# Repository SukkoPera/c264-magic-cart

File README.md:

# c264-magic-cart 44-pin

c264-magic-cart is a cartridge for the Commodore 264 series of computers - Commodore 16, 116 and Plus/4.

## Summary
This is a 44-pin variant of [the original project by Marko Šolajić](https://github.com/msolajic/c264-magic-cart).

This version is still aimed at the C16/C116/Plus4 and it **requires** the usage of a [Plus4MultiExpander](https://github.com/SukkoPera/Plus4MultiExpander) or something similar. It is NOT compatible with the C64/C128.

Isn't Open Hardware great?

## Usage
The project was migrated to KiCad, during which the nice graphics were lost. Apart from that and changing the connector, I only made minor modifications, mostly to switch to standard KiCad footprints.

The only significant difference is the introduction of JP4 and JP5 in order to run the cartridge from the C2 slot. This is experimental and untested, so just set them both to center-left in order to run from the C1 slot as the original project does.

If you plan to use this at the same time as the EPROM slot on [TCBM2SD](https://github.com/SukkoPera/tcbm2sd-44pin), you will probably need an updated JED file for the latter, which is yet unreleased at the time of writing, so please check again later.

Please refer to [the original project](https://github.com/msolajic/c264-magic-cart) for GAL files, documentation, instructions, etc.

## Releases
If you want to get this board produced, you are recommended to get [the latest release](https://github.com/SukkoPera/c264-magic-cart-44pin/releases) rather than the current git version, as the latter might be under development and is not guaranteed to be working.

Every release is accompanied by its Bill Of Materials (BOM) file and any relevant notes about it, which you are recommended to read carefully.

## License
The original c264-magic-cart is Open Hardware licensed under the [CERN OHL v. 1.2](https://spdx.org/licenses/CERN-OHL-1.2.html), released by Marko Šolajić in 2021.

This 44-pin version is copyright &copy; SukkoPera 2026 and is licensed under the same license.

## Thanks
- Marko for his amazing work.
- Tadeusz Klimaszewski for coming up with the idea of porting this project to the 44-pin connector and testing it.

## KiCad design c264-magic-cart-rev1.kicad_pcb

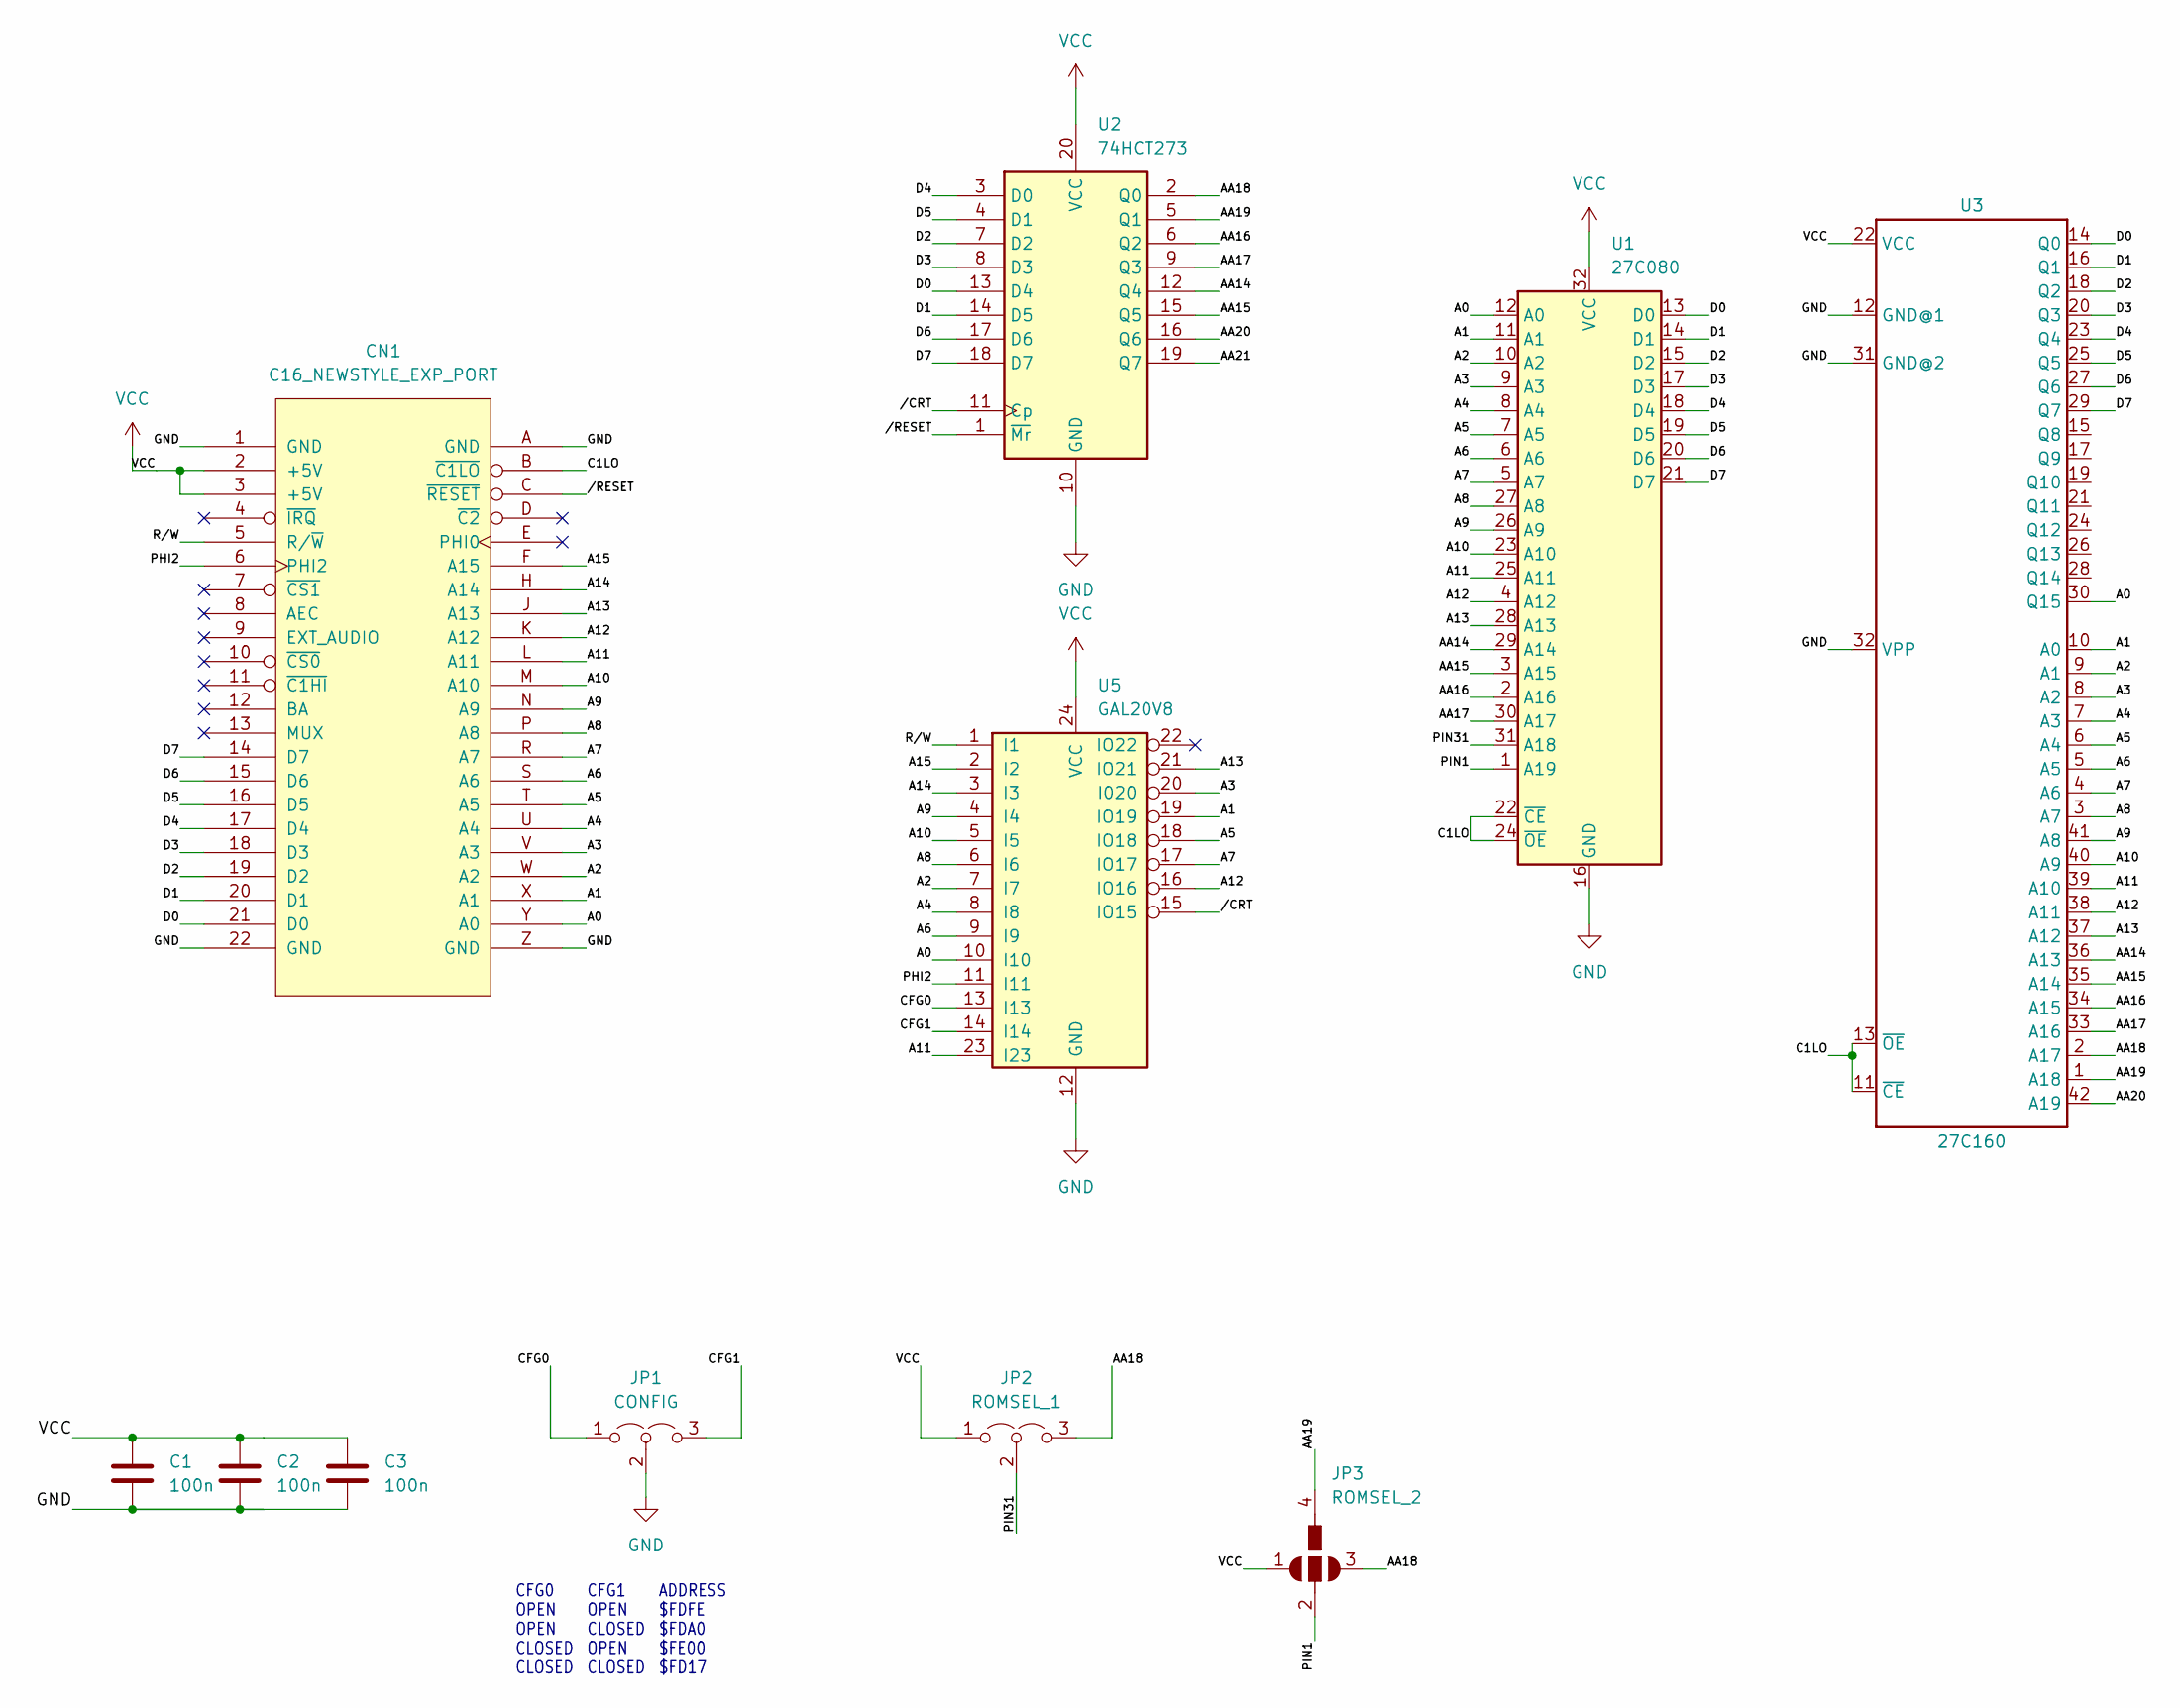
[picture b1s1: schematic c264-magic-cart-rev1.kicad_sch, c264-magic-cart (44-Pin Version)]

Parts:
C1, C2, C3: 100n; C_Disc_D7.5mm_W2.5mm_P5.00mm
CN1: C16_NEWSTYLE_EXP_PORT; EdgeConn-44pin
JP1: CONFIG; SolderJumper-3_P1.3mm_Open_Pad1.0x1.5mm
JP2: ROMSEL_1; SolderJumper-3_P1.3mm_Open_Pad1.0x1.5mm
JP3: ROMSEL_2; SJ_3
U1: 27C080; DIP-32_W15.24mm_Socket
U2: 74HCT273; DIP-20_W7.62mm_Socket_LongPads
U3: 27C160; DIP-42_W15.24mm_Socket
U5: GAL20V8; DIP-24_W7.62mm_Socket_LongPads

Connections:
/A0: CN1.Y (A0), U1.12 (A0), U3.30 (Q15), U5.10 (I10)
/A1: CN1.X (A1), U1.11 (A1), U3.10 (A0), U5.19 (IO19)
/A2: CN1.W (A2), U1.10 (A2), U3.9 (A1), U5.7 (I7)
/A3: CN1.V (A3), U1.9 (A3), U3.8 (A2), U5.20 (I020)
/A4: CN1.U (A4), U1.8 (A4), U3.7 (A3), U5.8 (I8)
/A5: CN1.T (A5), U1.7 (A5), U3.6 (A4), U5.18 (IO18)
/A6: CN1.S (A6), U1.6 (A6), U3.5 (A5), U5.9 (I9)
/A7: CN1.R (A7), U1.5 (A7), U3.4 (A6), U5.17 (IO17)
/A8: CN1.P (A8), U1.27 (A8), U3.3 (A7), U5.6 (I6)
/A9: CN1.N (A9), U1.26 (A9), U3.41 (A8), U5.4 (I4)
/A10: CN1.M (A10), U1.23 (A10), U3.40 (A9), U5.5 (I5)
/A11: CN1.L (A11), U1.25 (A11), U3.39 (A10), U5.23 (I23)
/A12: CN1.K (A12), U1.4 (A12), U3.38 (A11), U5.16 (IO16)
/A13: CN1.J (A13), U1.28 (A13), U3.37 (A12), U5.21 (IO21)
/A14: CN1.H (A14), U5.3 (I3)
/A15: CN1.F (A15), U5.2 (I2)
/AA14: U1.29 (A14), U2.12 (Q4), U3.36 (A13)
/AA15: U1.3 (A15), U2.15 (Q5), U3.35 (A14)
/AA16: U1.2 (A16), U2.6 (Q2), U3.34 (A15)
/AA17: U1.30 (A17), U2.9 (Q3), U3.33 (A16)
/AA18: JP2.3 (B), JP3.3, U2.2 (Q0), U3.2 (A17)
/AA19: JP3.4, U2.5 (Q1), U3.1 (A18)
/AA20: U2.16 (Q6), U3.42 (A19)
/AA21: U2.19 (Q7)
/C1LO: CN1.B (~C1LO), U1.22 (~CE), U1.24 (~OE), U3.11 (~CE), U3.13 (~OE)
/CFG0: JP1.1 (A), U5.13 (I13)
/CFG1: JP1.3 (B), U5.14 (I14)
/D0: CN1.21 (D0), U1.13 (D0), U2.13 (D4), U3.14 (Q0)
/D1: CN1.20 (D1), U1.14 (D1), U2.14 (D5), U3.16 (Q1)
/D2: CN1.19 (D2), U1.15 (D2), U2.7 (D2), U3.18 (Q2)
/D3: CN1.18 (D3), U1.17 (D3), U2.8 (D3), U3.20 (Q3)
/D4: CN1.17 (D4), U1.18 (D4), U2.3 (D0), U3.23 (Q4)
/D5: CN1.16 (D5), U1.19 (D5), U2.4 (D1), U3.25 (Q5)
/D6: CN1.15 (D6), U1.20 (D6), U2.17 (D6), U3.27 (Q6)
/D7: CN1.14 (D7), U1.21 (D7), U2.18 (D7), U3.29 (Q7)
/PHI2: CN1.6 (PHI2), U5.11 (I11)
/PIN1: JP3.2, U1.1 (A19)
/PIN31: JP2.2 (C), U1.31 (A18)
/R/W: CN1.5 (R/~W), U5.1 (I1)
//CRT: U2.11 (Cp), U5.15 (IO15)
//RESET: CN1.C (~RESET), U2.1 (~Mr)
GND: C1.2, C2.2, C3.2, CN1.1 (GND), CN1.22 (GND), CN1.A (GND), CN1.Z (GND), JP1.2 (C), U1.16 (GND), U2.10 (GND), U3.12 (GND@1), U3.31 (GND@2), U3.32 (VPP), U5.12 (GND)
VCC: C1.1, C2.1, C3.1, CN1.2 (+5V), CN1.3 (+5V), JP2.1 (A), JP3.1, U1.32 (VCC), U2.20 (VCC), U3.22 (VCC), U5.24 (VCC)

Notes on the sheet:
ADDRESS $FDFE $FDA0 $FE00 $FD17
CFG1 OPEN CLOSED OPEN CLOSED
CFG0 OPEN OPEN CLOSED CLOSED

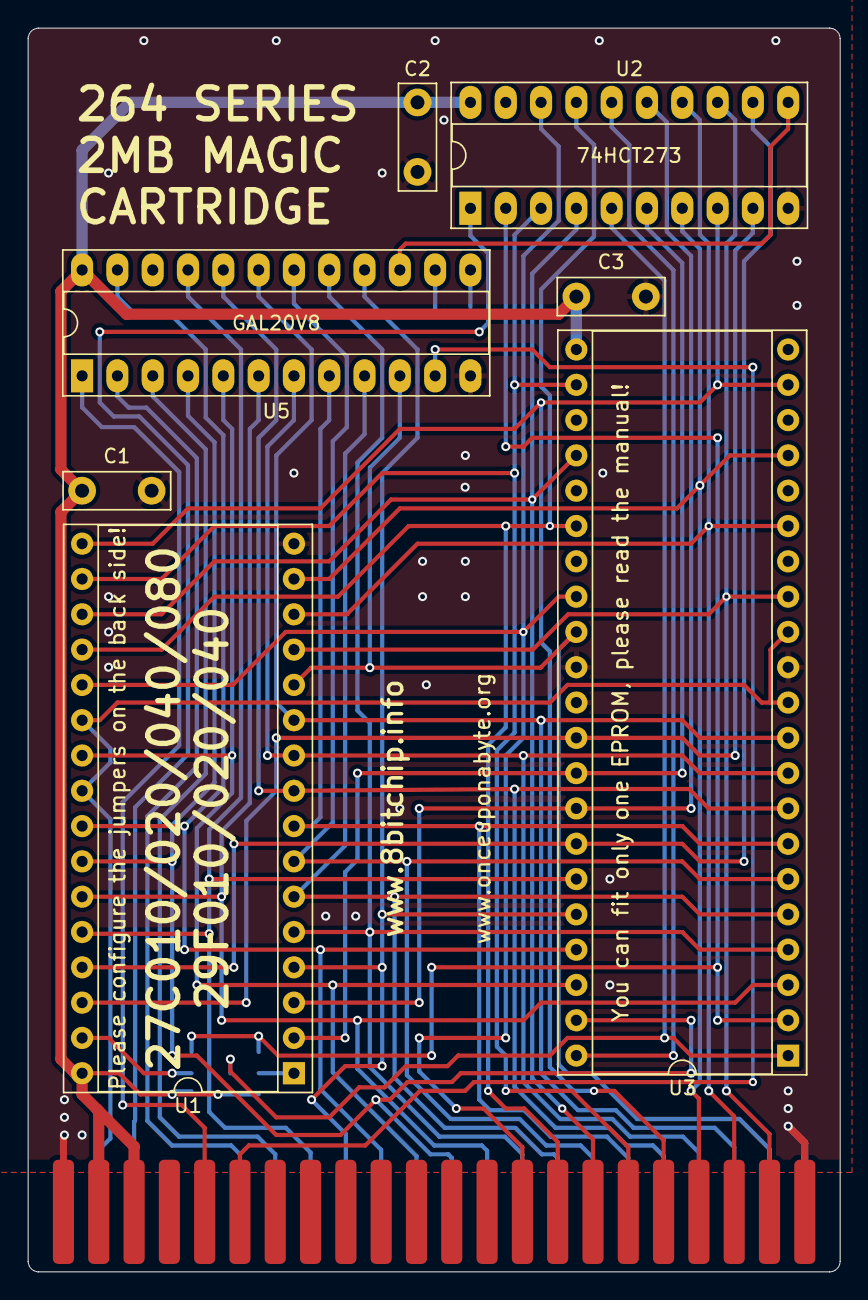
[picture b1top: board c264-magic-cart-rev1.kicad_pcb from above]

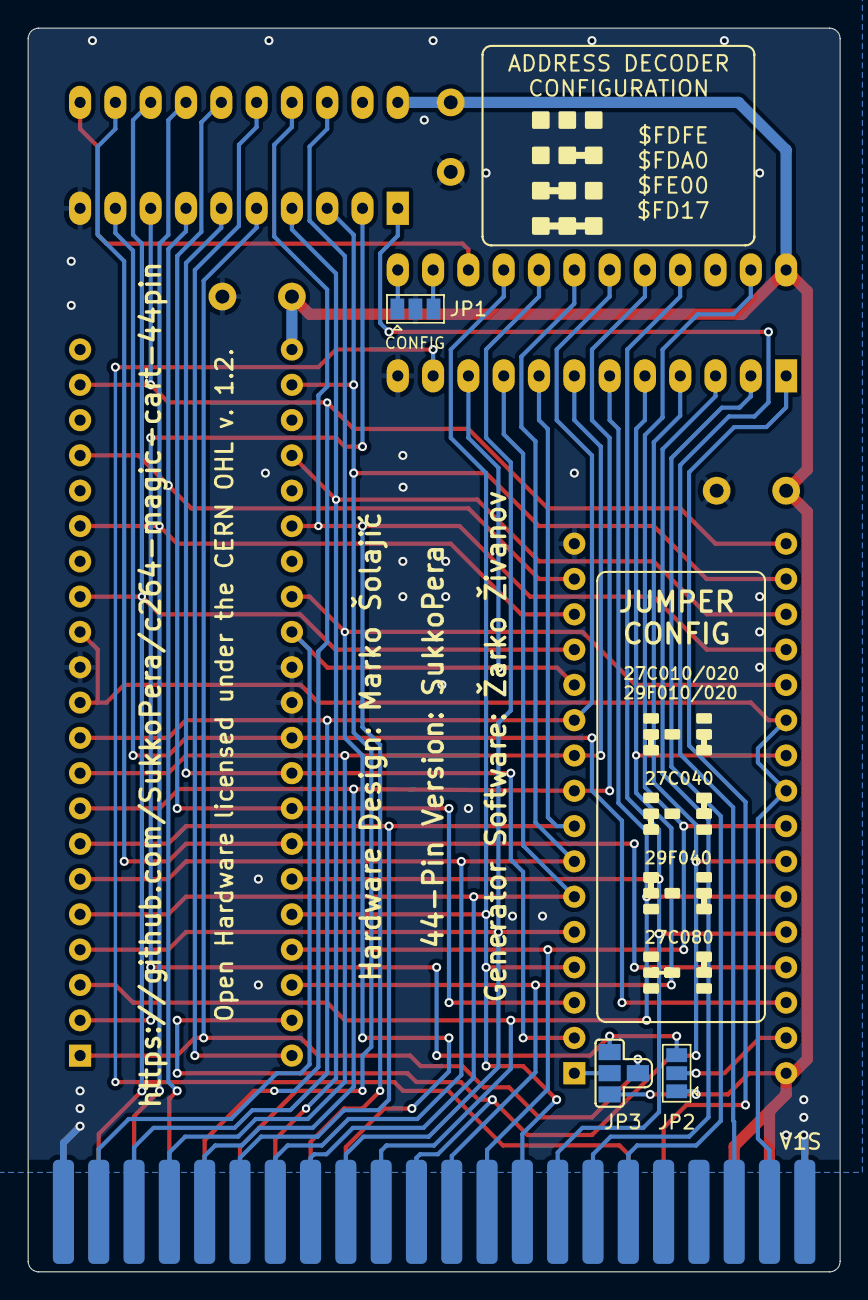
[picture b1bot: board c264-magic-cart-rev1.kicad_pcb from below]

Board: 2 copper layers, 58.4 x 89.5 mm, 11 parts (3 on the bottom side), 42 nets.

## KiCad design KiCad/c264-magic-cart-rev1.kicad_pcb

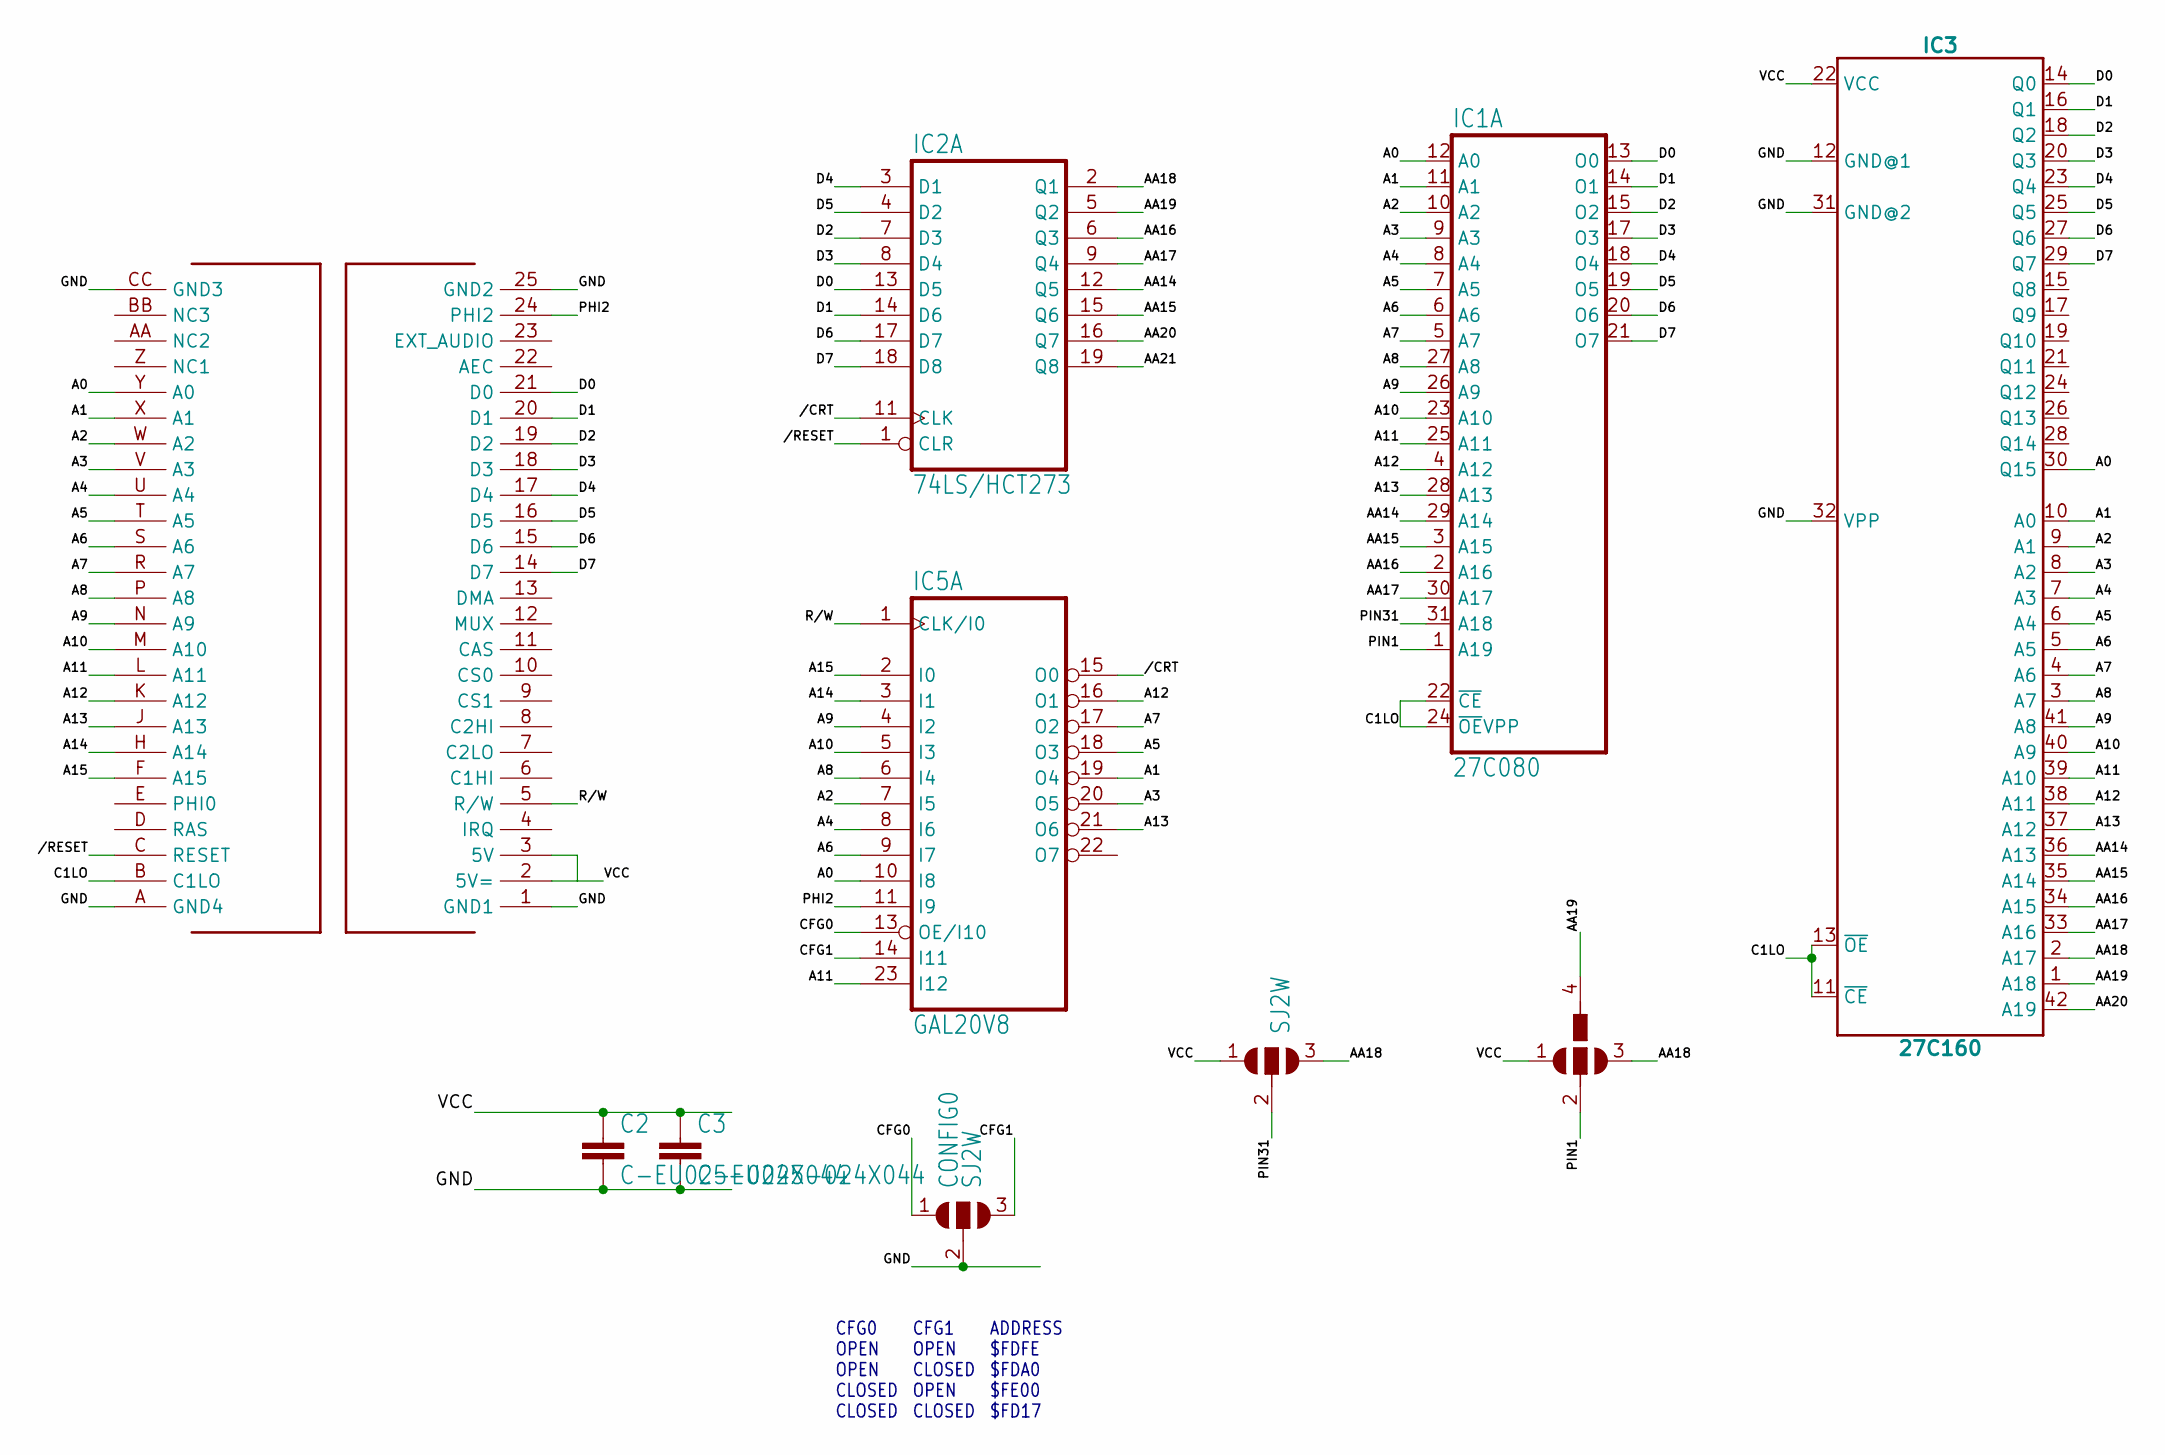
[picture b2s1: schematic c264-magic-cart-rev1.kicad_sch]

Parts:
C2, C3: C-EU025-024X044; C025-024X044
CONFIG0: SJ2W; SJ_2
IC1: 27C080; DIL32
IC2: 74LS/HCT273; DIL20
IC3: 27C160; DIP42
IC5: GAL20V8; DIL24-3
SJ1: SJ2W; SJ_2
U$1: C16_CARTRIDGE; C16_CART
U$2: SJ3; SJ_3

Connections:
/CRT: IC2.11 (CLK), IC5.15 (O0)
/RESET: IC2.1 (CLR), U$1.C (RESET)
A0: IC1.12 (A0), IC3.30 (Q15), IC5.10 (I8), U$1.Y (A0)
A1: IC1.11 (A1), IC3.10 (A0), IC5.19 (O4), U$1.X (A1)
A2: IC1.10 (A2), IC3.9 (A1), IC5.7 (I5), U$1.W (A2)
A3: IC1.9 (A3), IC3.8 (A2), IC5.20 (O5), U$1.V (A3)
A4: IC1.8 (A4), IC3.7 (A3), IC5.8 (I6), U$1.U (A4)
A5: IC1.7 (A5), IC3.6 (A4), IC5.18 (O3), U$1.T (A5)
A6: IC1.6 (A6), IC3.5 (A5), IC5.9 (I7), U$1.S (A6)
A7: IC1.5 (A7), IC3.4 (A6), IC5.17 (O2), U$1.R (A7)
A8: IC1.27 (A8), IC3.3 (A7), IC5.6 (I4), U$1.P (A8)
A9: IC1.26 (A9), IC3.41 (A8), IC5.4 (I2), U$1.N (A9)
A10: IC1.23 (A10), IC3.40 (A9), IC5.5 (I3), U$1.M (A10)
A11: IC1.25 (A11), IC3.39 (A10), IC5.23 (I12), U$1.L (A11)
A12: IC1.4 (A12), IC3.38 (A11), IC5.16 (O1), U$1.K (A12)
A13: IC1.28 (A13), IC3.37 (A12), IC5.21 (O6), U$1.J (A13)
A14: IC5.3 (I1), U$1.H (A14)
A15: IC5.2 (I0), U$1.F (A15)
AA14: IC1.29 (A14), IC2.12 (Q5), IC3.36 (A13)
AA15: IC1.3 (A15), IC2.15 (Q6), IC3.35 (A14)
AA16: IC1.2 (A16), IC2.6 (Q3), IC3.34 (A15)
AA17: IC1.30 (A17), IC2.9 (Q4), IC3.33 (A16)
AA18: IC2.2 (Q1), IC3.2 (A17), SJ1.3, U$2.3
AA19: IC2.5 (Q2), IC3.1 (A18), U$2.4
AA20: IC2.16 (Q7), IC3.42 (A19)
AA21: IC2.19 (Q8)
C1LO: IC1.22 (~CE), IC1.24 (~OEVPP), IC3.11 (~CE), IC3.13 (~OE), U$1.B (C1LO)
CFG0: CONFIG0.1, IC5.13 (OE/I10)
CFG1: CONFIG0.3, IC5.14 (I11)
D0: IC1.13 (O0), IC2.13 (D5), IC3.14 (Q0), U$1.21 (D0)
D1: IC1.14 (O1), IC2.14 (D6), IC3.16 (Q1), U$1.20 (D1)
D2: IC1.15 (O2), IC2.7 (D3), IC3.18 (Q2), U$1.19 (D2)
D3: IC1.17 (O3), IC2.8 (D4), IC3.20 (Q3), U$1.18 (D3)
D4: IC1.18 (O4), IC2.3 (D1), IC3.23 (Q4), U$1.17 (D4)
D5: IC1.19 (O5), IC2.4 (D2), IC3.25 (Q5), U$1.16 (D5)
D6: IC1.20 (O6), IC2.17 (D7), IC3.27 (Q6), U$1.15 (D6)
D7: IC1.21 (O7), IC2.18 (D8), IC3.29 (Q7), U$1.14 (D7)
GND: C2.2, C3.2, CONFIG0.2, IC1.16 (GND), IC2.10 (GND), IC3.12 (GND@1), IC3.31 (GND@2), IC3.32 (VPP), IC5.12 (GND), U$1.1 (GND1), U$1.25 (GND2), U$1.A (GND4), U$1.CC (GND3)
PHI2: IC5.11 (I9), U$1.24 (PHI2)
PIN1: IC1.1 (A19), U$2.2
PIN31: IC1.31 (A18), SJ1.2
R/W: IC5.1 (CLK/I0), U$1.5 (R/W)
VCC: C2.1, C3.1, IC1.32 (VCC), IC2.20 (VCC), IC3.22 (VCC), IC5.24 (VCC), SJ1.1, U$1.2 (5V=), U$1.3 (5V), U$2.1

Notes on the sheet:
ADDRESS $FDFE $FDA0 $FE00 $FD17
CFG1 OPEN CLOSED OPEN CLOSED
CFG0 OPEN OPEN CLOSED CLOSED

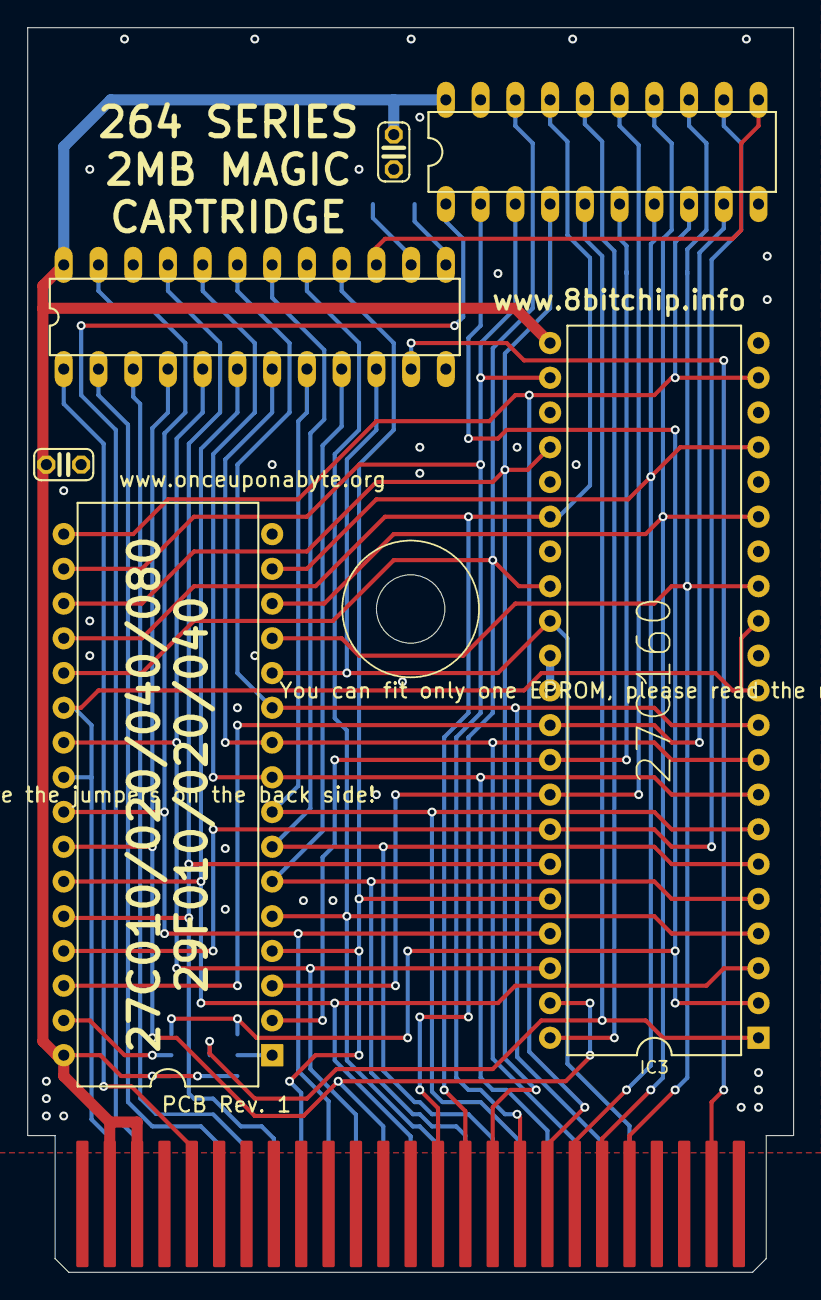
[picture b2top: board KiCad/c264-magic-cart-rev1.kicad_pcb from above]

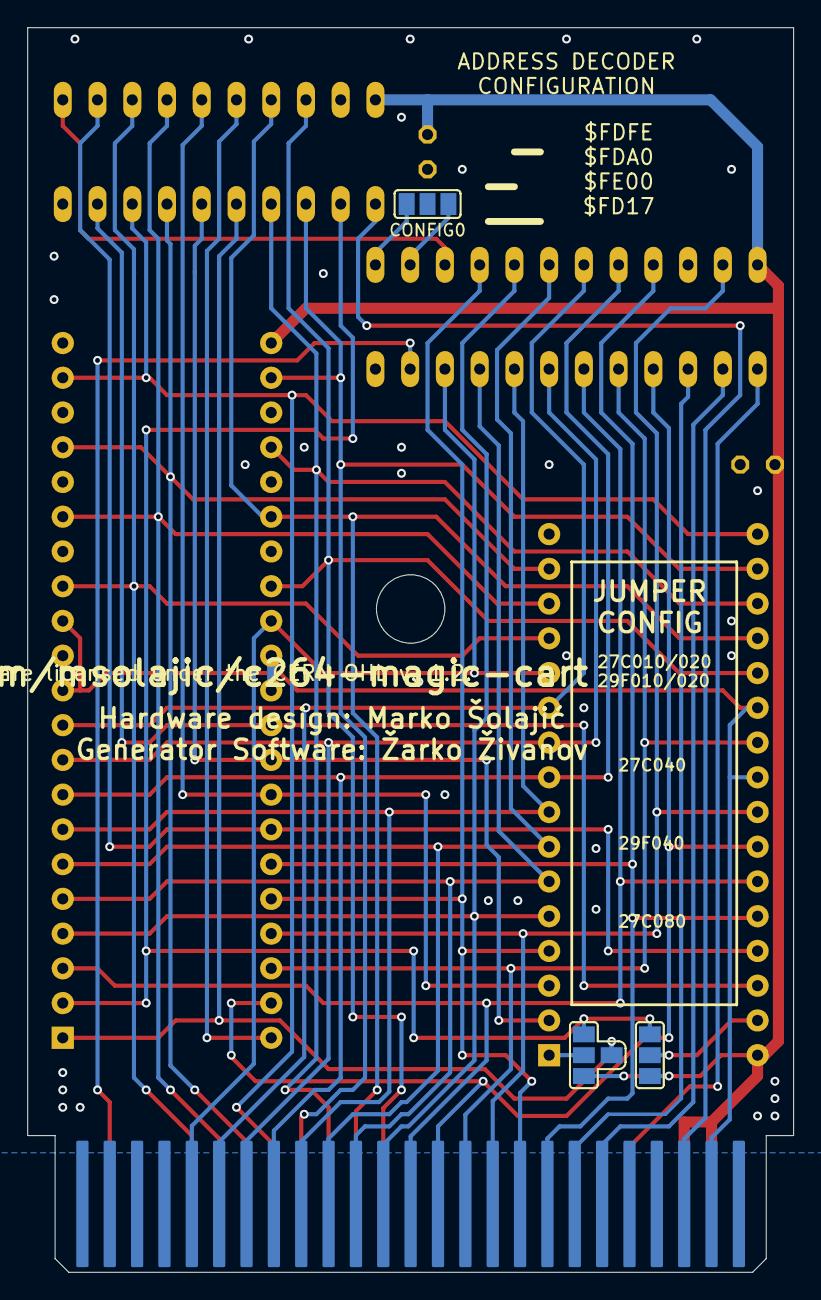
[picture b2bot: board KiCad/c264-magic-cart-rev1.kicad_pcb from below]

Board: 2 copper layers, 56.0 x 91.0 mm, 10 parts (3 on the bottom side), 42 nets.

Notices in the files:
c264-magic-cart-rev1.kicad_pcb:
Licensed under CERN OHL v.1.2
